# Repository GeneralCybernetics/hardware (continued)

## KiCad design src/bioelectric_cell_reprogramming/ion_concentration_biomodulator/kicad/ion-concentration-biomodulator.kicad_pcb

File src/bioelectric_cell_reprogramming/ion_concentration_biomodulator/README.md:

# Ion Concentration Biomodulator (v5)

The purpose of the chip is to enable an incubator to dispense ions over a cellular culture within the incubator.

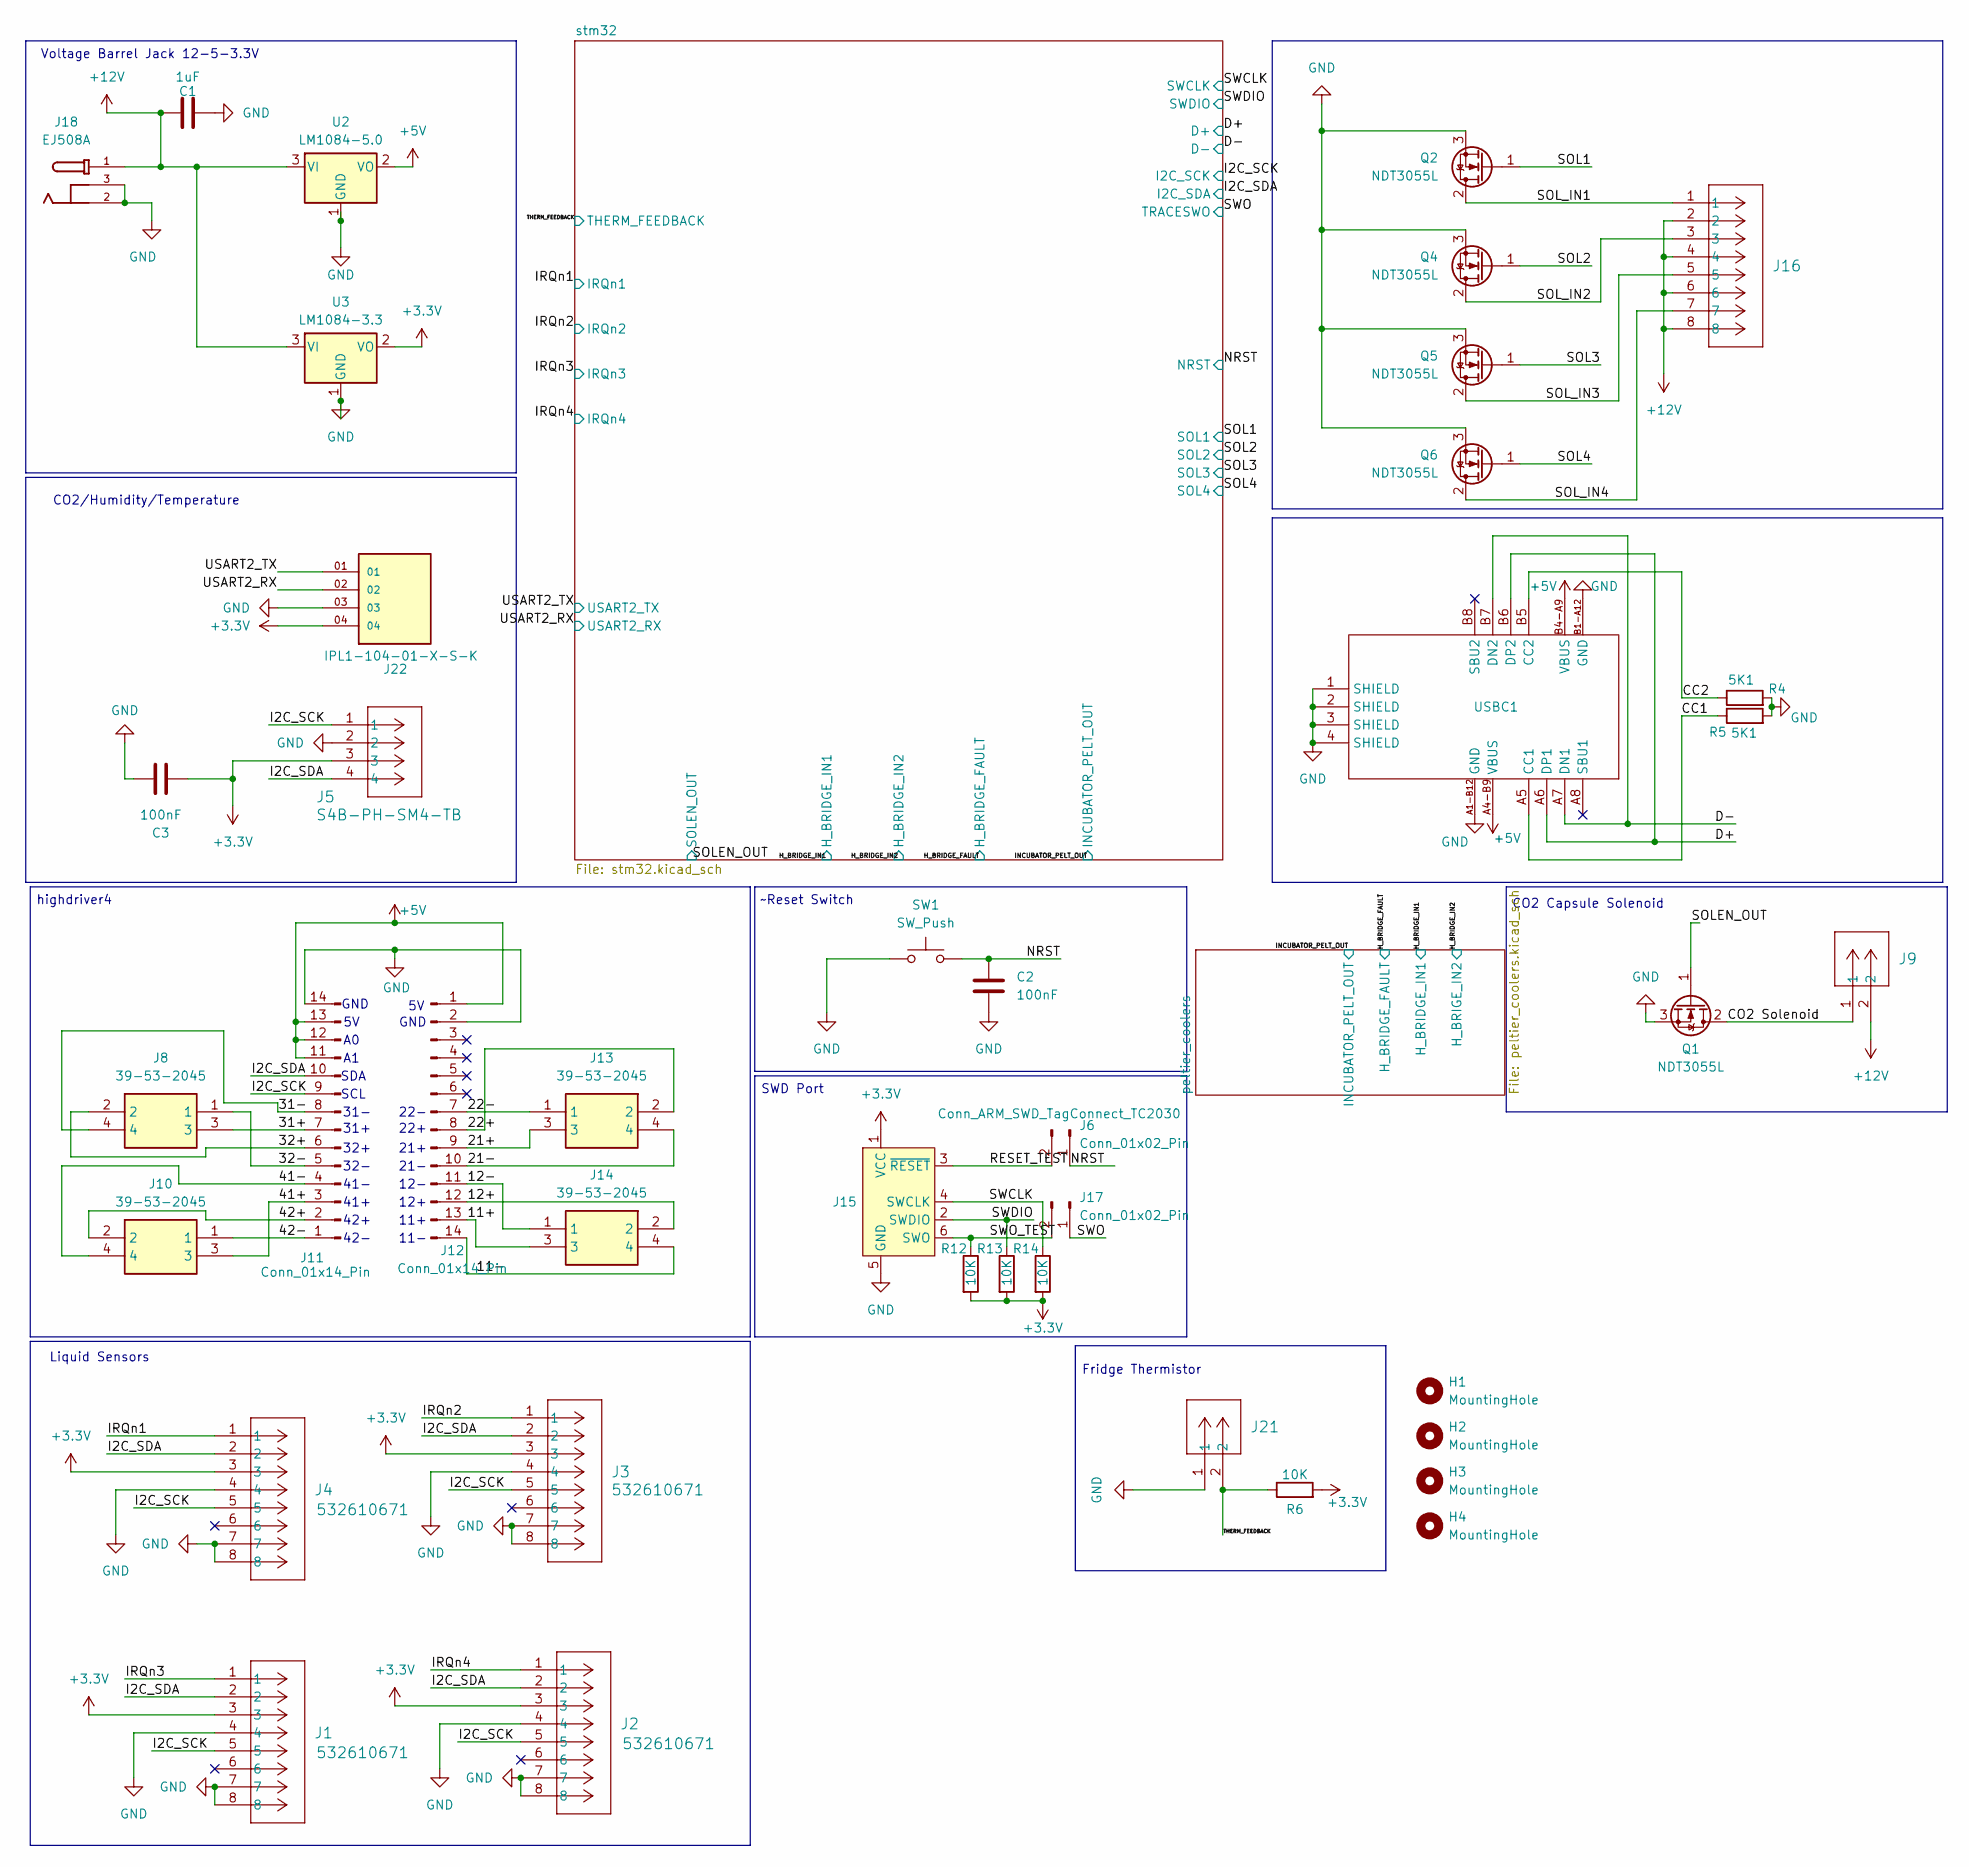
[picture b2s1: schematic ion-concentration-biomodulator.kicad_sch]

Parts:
C1: 1uF; C_1812_4532Metric
C2, C3: 100nF; C_0201_0603Metric
H1, H2, H3, H4: MountingHole; MountingHole_2.2mm_M2
J1, J2, J3, J4: 532610671; CON_532610671
J5: S4B-PH-SM4-TB; CONN4_S4B-PH-SM4-TB_JST
J6, J17: Conn_01x02_Pin; PinHeader_1x02_P2.00mm_Vertical
J8, J10, J13, J14: 39-53-2045; 39532045; Mouser Part Number 538-39532045
J9, J21: IPL1-102-01-L-S-K; CONN_IPL1-102-01-L-S-K_SAI
J11, J12: Conn_01x14_Pin; PinSocket_1x14_P2.54mm_Vertical
J15: Conn_ARM_SWD_TagConnect_TC2030; Tag-Connect_TC2030-IDC-FP_2x03_P1.27mm_Vertical
J16: IPL1-104-01-L-D-K; CONN_IPL1-104-01-x-D-x_SAI
J18: EJ508A; MPD_EJ508A; PARTREV J
J22: IPL1-104-01-X-S-K; SAMTEC_IPL1-104-01-X-S-K; PARTREV E
Q1, Q2, Q4, Q5, Q6: NDT3055L; SOT-223-3_TabPin2
R4, R5: 5K1; R_0603_1608Metric
R6, R12, R13, R14: 10K; R_0201_0603Metric
SW1: SW_Push; SW_PUSH-12mm_Wuerth-430476085716
U2: LM1084-5.0; TO254P1524X483-4N
U3: LM1084-3.3; TO254P1524X483-4N
USBC1: USB-C-SMD_MC-311D; Manufacturer Part MC-311D; LCSC Part Name Type-C 母

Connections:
+3.3V: C3.1, J1.3, J2.3, J3.3, J4.3, J5.3, J15.1 (VCC), J22.04, R6.2, R12.2, R13.2, R14.2, U3.2 (VO); also elsewhere on the board
+5V: J11.11, J11.12, J11.13, J12.1, U2.2 (VO), USBC1.A4-B9 (VBUS), USBC1.B4-A9 (VBUS); also elsewhere on the board
+12V: C1.1, J9.2, J16.2, J16.4, J16.6, J16.8, J18.1, U2.3 (VI), U3.3 (VI); also elsewhere on the board
/11+: J12.13, J14.3
/11-: J12.14, J14.4
/12+: J12.12, J14.2
/12-: J12.11, J14.1
/21+: J12.9, J13.3
/21-: J12.10, J13.4
/22+: J12.8, J13.2
/22-: J12.7, J13.1
/31+: J8.3, J11.7
/31-: J8.4, J11.8
/32+: J8.2, J11.6
/32-: J8.1, J11.5
/41+: J10.3, J11.3
/41-: J10.4, J11.4
/42+: J10.2, J11.2
/42-: J10.1, J11.1
/CC1: R4.1, USBC1.B5 (CC2); also elsewhere on the board
/CC2: R5.1, USBC1.A5 (CC1); also elsewhere on the board
/CO2 Solenoid: J9.1, Q1.2 (D)
/I2C_SCK: J1.5, J2.5, J3.5, J4.5, J5.1, J11.9; also elsewhere on the board
/I2C_SDA: J1.2, J2.2, J3.2, J4.2, J5.4, J11.10; also elsewhere on the board
/IRQn1: J4.1; also elsewhere on the board
/IRQn2: J3.1; also elsewhere on the board
/IRQn3: J1.1; also elsewhere on the board
/IRQn4: J2.1; also elsewhere on the board
/NRST: C2.1, J6.1, SW1.2; also elsewhere on the board
/RESET_TEST: J6.2, J15.3 (~RESET)
/SOL1: Q2.1 (G); also elsewhere on the board
/SOL2: Q4.1 (G); also elsewhere on the board
/SOL3: Q5.1 (G); also elsewhere on the board
/SOL4: Q6.1 (G); also elsewhere on the board
/SOLEN_OUT: Q1.1 (G); also elsewhere on the board
/SOL_IN1: J16.1, Q2.2 (D)
/SOL_IN2: J16.3, Q4.2 (D)
/SOL_IN3: J16.5, Q5.2 (D)
/SOL_IN4: J16.7, Q6.2 (D)
/SWCLK: J15.4 (SWCLK), R14.1; also elsewhere on the board
/SWDIO: J15.2 (SWDIO), R13.1; also elsewhere on the board
/SWO: J17.1; also elsewhere on the board
/SWO_TEST: J15.6 (SWO), J17.2, R12.1
/THERM_FEEDBACK: J21.2, R6.1; also elsewhere on the board
/USART2_RX: J22.02; also elsewhere on the board
/USART2_TX: J22.01; also elsewhere on the board
GND: C1.2, C2.2, C3.2, J1.4, J1.7, J1.8, J2.4, J2.7, J2.8, J3.4, J3.7, J3.8, J4.4, J4.7, J4.8, J5.2, J11.14, J12.2, J15.5 (GND), J18.2, J18.3, J21.1, J22.03, Q1.3 (S), Q2.3 (S), Q4.3 (S), Q5.3 (S), Q6.3 (S), R4.2, R5.2, SW1.1, U2.1 (GND), U3.1 (GND), USBC1.1 (SHIELD), USBC1.2 (SHIELD), USBC1.3 (SHIELD), USBC1.4 (SHIELD), USBC1.A1-B12 (GND), USBC1.B1-A12 (GND); also elsewhere on the board
unnamed: USBC1.A6 (DP1), USBC1.B6 (DP2)
unnamed: USBC1.A7 (DN1), USBC1.B7 (DN2)

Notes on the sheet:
Voltage Barrel Jack 12-5-3.3V
21+
CO2/Humidity/Temperature
41+
31-
SDA
Fridge Thermistor
SWD Port
41-
GND
32-
SCL
42-
Liquid Sensors
11-
22+
highdriver4
12-
21-
~Reset Switch
32+
22-
CO2 Capsule Solenoid
11+
42+
31+
12+

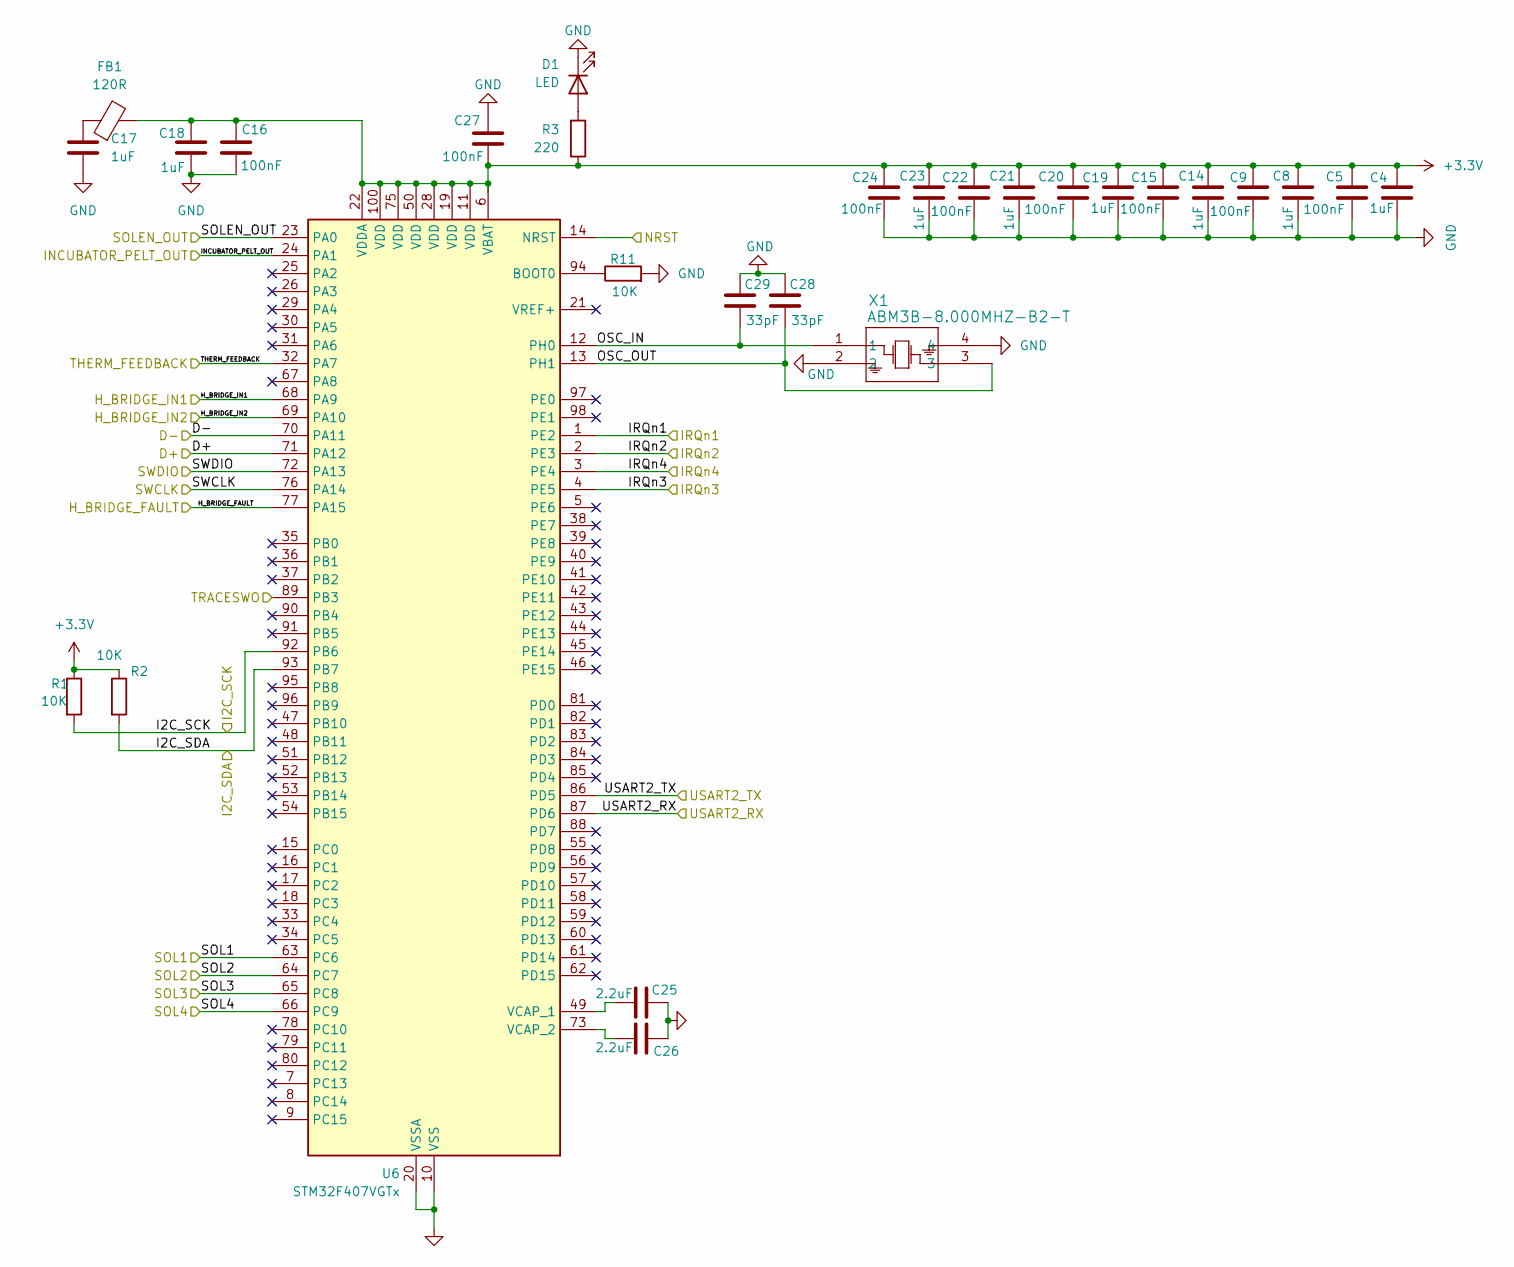
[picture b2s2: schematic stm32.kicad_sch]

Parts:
C4, C8, C14, C17, C18, C19, C21, C23: 1uF; C_0201_0603Metric
C5, C9, C15, C16, C20, C22, C24, C27: 100nF; C_0201_0603Metric
C25, C26: 2.2uF; C_0201_0603Metric
C28, C29: 33pF; C_0201_0603Metric
D1: LED; LED_0201_0603Metric
FB1: 120R; L_0603_1608Metric
R1, R2, R11: 10K; R_0201_0603Metric
R3: 220; R_0201_0603Metric
U6: STM32F407VGTx; LQFP-100_14x14mm_P0.5mm
X1: ABM3B-8.000MHZ-B2-T; ABM3B_ABR

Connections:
+3.3V: C4.1, C5.1, C8.1, C9.1, C14.1, C15.1, C16.1, C18.1, C19.1, C20.1, C21.1, C22.1, C23.1, C24.1, C27.2, FB1.2, R1.1, R2.1, R3.1, U6.6 (VBAT), U6.11 (VDD), U6.19 (VDD), U6.22 (VDDA), U6.28 (VDD), U6.50 (VDD), U6.75 (VDD), U6.100 (VDD); also elsewhere on the board
/D+: U6.71 (PA12); also elsewhere on the board
/D-: U6.70 (PA11); also elsewhere on the board
/H_BRIDGE_FAULT: U6.77 (PA15); also elsewhere on the board
/H_BRIDGE_IN1: U6.68 (PA9); also elsewhere on the board
/H_BRIDGE_IN2: U6.69 (PA10); also elsewhere on the board
/I2C_SCK: R1.2, U6.92 (PB6); also elsewhere on the board
/I2C_SDA: R2.2, U6.93 (PB7); also elsewhere on the board
/INCUBATOR_PELT_OUT: U6.24 (PA1); also elsewhere on the board
/IRQn1: U6.1 (PE2); also elsewhere on the board
/IRQn2: U6.2 (PE3); also elsewhere on the board
/IRQn3: U6.4 (PE5); also elsewhere on the board
/IRQn4: U6.3 (PE4); also elsewhere on the board
/NRST: U6.14 (NRST); also elsewhere on the board
/SOL1: U6.63 (PC6); also elsewhere on the board
/SOL2: U6.64 (PC7); also elsewhere on the board
/SOL3: U6.65 (PC8); also elsewhere on the board
/SOL4: U6.66 (PC9); also elsewhere on the board
/SOLEN_OUT: U6.23 (PA0); also elsewhere on the board
/SWCLK: U6.76 (PA14); also elsewhere on the board
/SWDIO: U6.72 (PA13); also elsewhere on the board
/SWO: U6.89 (PB3); also elsewhere on the board
/THERM_FEEDBACK: U6.32 (PA7); also elsewhere on the board
/USART2_RX: U6.87 (PD6); also elsewhere on the board
/USART2_TX: U6.86 (PD5); also elsewhere on the board
/stm32/OSC_IN: C29.2, U6.12 (PH0), X1.1
/stm32/OSC_OUT: C28.2, U6.13 (PH1), X1.3
GND: C4.2, C5.2, C8.2, C9.2, C14.2, C15.2, C16.2, C17.2, C18.2, C19.2, C20.2, C21.2, C22.2, C23.2, C24.2, C25.2, C26.2, C27.1, C28.1, C29.1, D1.1 (K), R11.2, U6.10 (VSS), U6.20 (VSSA), U6.27 (VSS), U6.74 (VSS), U6.99 (VSS), X1.2, X1.4; also elsewhere on the board
unnamed: C17.1, FB1.1
unnamed: D1.2 (A), R3.2
unnamed: R11.1, U6.94 (BOOT0)
unnamed: C25.1, U6.49 (VCAP_1)
unnamed: C26.1, U6.73 (VCAP_2)

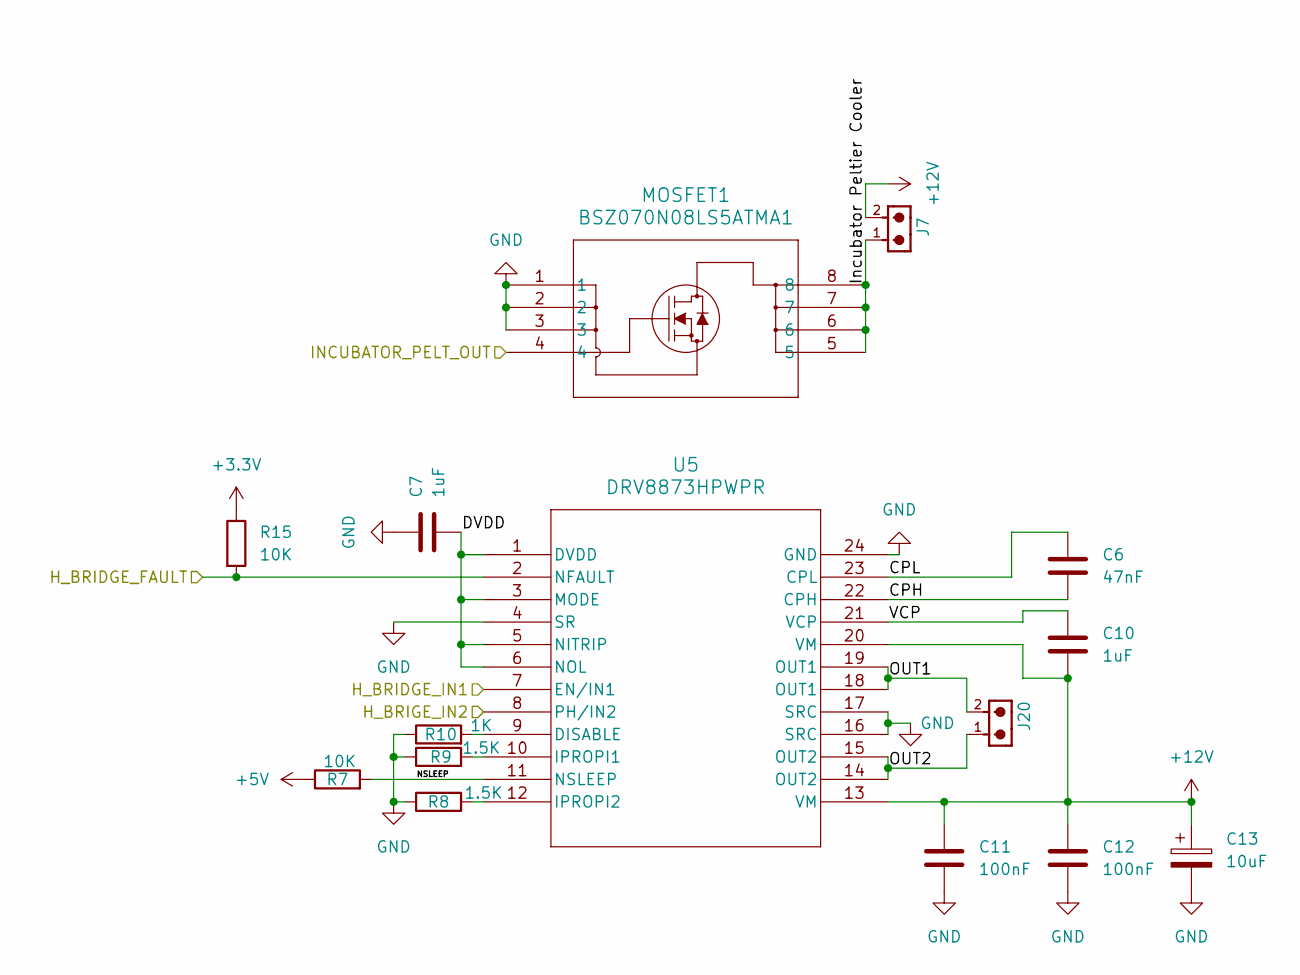
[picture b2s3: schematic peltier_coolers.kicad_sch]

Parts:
C6: 47nF; C_0402_1005Metric
C7: 1uF; C_0201_0603Metric
C10: 1uF; C_0402_1005Metric
C11, C12: 100nF; C_0402_1005Metric
C13: 10uF; CP_Elec_3x5.3
J7, J20: 6620XX11122_66200211122; 66200211122; PART-NUMBER 66200211122
MOSFET1: BSZ070N08LS5ATMA1; TSDSON-8-FL_INF
R7, R15: 10K; R_0201_0603Metric
R8, R9: 1.5K; R_0201_0603Metric
R10: 1K; R_0201_0603Metric
U5: DRV8873HPWPR; PWP24_TEX

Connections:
+3.3V: R15.1; also elsewhere on the board
+5V: R7.1; also elsewhere on the board
+12V: C10.2, C11.1, C12.1, C13.1, J7.2, U5.13 (VM), U5.20 (VM); also elsewhere on the board
/H_BRIDGE_FAULT: R15.2, U5.2 (NFAULT); also elsewhere on the board
/H_BRIDGE_IN1: U5.7 (EN/IN1); also elsewhere on the board
/H_BRIDGE_IN2: U5.8 (PH/IN2); also elsewhere on the board
/INCUBATOR_PELT_OUT: MOSFET1.4; also elsewhere on the board
/peltier_coolers/CPH: C6.2, U5.22 (CPH)
/peltier_coolers/CPL: C6.1, U5.23 (CPL)
/peltier_coolers/DVDD: C7.2, U5.1 (DVDD), U5.3 (MODE), U5.5 (NITRIP), U5.6 (NOL)
/peltier_coolers/Incubator Peltier Cooler: J7.1, MOSFET1.5, MOSFET1.6, MOSFET1.7, MOSFET1.8
/peltier_coolers/NSLEEP: R7.2, U5.11 (NSLEEP)
/peltier_coolers/OUT1: J20.2, U5.18 (OUT1), U5.19 (OUT1)
/peltier_coolers/OUT2: J20.1, U5.14 (OUT2), U5.15 (OUT2)
/peltier_coolers/VCP: C10.1, U5.21 (VCP)
GND: C7.1, C11.2, C12.2, C13.2, MOSFET1.1, MOSFET1.2, MOSFET1.3, R8.1, R9.1, R10.1, U5.4 (SR), U5.16 (SRC), U5.17 (SRC), U5.24 (GND); also elsewhere on the board
unnamed: R10.2, U5.9 (DISABLE)
unnamed: R9.2, U5.10 (IPROPI1)
unnamed: R8.2, U5.12 (IPROPI2)

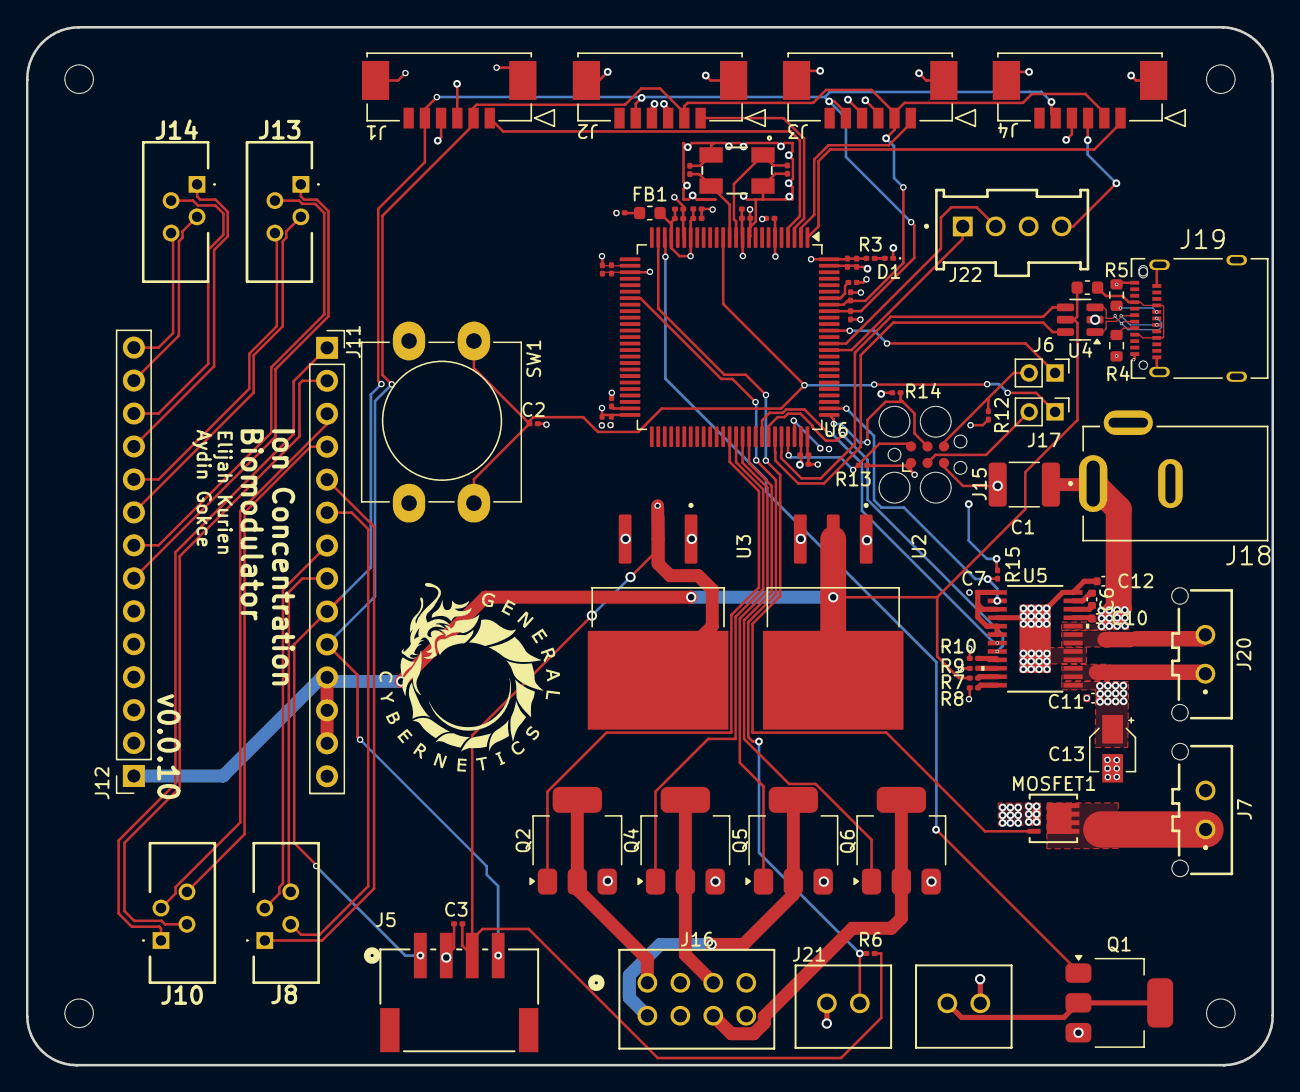
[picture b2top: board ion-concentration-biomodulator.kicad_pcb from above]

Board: 4 copper layers, 96.0 x 80.0 mm, 86 parts (0 on the bottom side), 74 nets.

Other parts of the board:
F1: 500mA; Fuse_0603_1608Metric
J19: USB_C_Receptacle_USB2.0_14P; AMPHENOL_12401610E4_2A
U4: USBLC6-2SC6; SOT-23-6

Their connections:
+5V: F1.2, U4.5 (VBUS); also elsewhere on the board
/CC1: J19.A5 (CC1); also elsewhere on the board
/CC2: J19.B5 (CC2); also elsewhere on the board
/D+: U4.4 (I/O2); also elsewhere on the board
/D+_in: J19.A6 (DA+), J19.B6 (DB+), U4.3 (I/O2)
/D-: U4.6 (I/O1); also elsewhere on the board
/D-_in: J19.A7 (DA-), J19.B7 (DB-), U4.1 (I/O1)
/VBUS: F1.1, J19.A4 (VBUS_A4), J19.A9 (VBUS_A9), J19.B4 (VBUS_B4), J19.B9 (VBUS_B9)
GND: J19.A1 (GND_A1), J19.A12 (GND_A12), J19.B1 (GND_B1), J19.B12 (GND_B12), J19.S1 (SHIELD), J19.S2 (SHIELD__1), J19.S3 (SHIELD__2), J19.S4 (SHIELD__3), U4.2 (GND); also elsewhere on the board

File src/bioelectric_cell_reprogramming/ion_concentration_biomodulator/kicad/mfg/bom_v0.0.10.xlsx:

Comment | Designator | Footprint | JLCPCB Part #
10K | R14,R13,R12,R11,R2,R1,R7,R6 | R_0201_0603Metric | C3152014
2.2uF | C26,C25 | C_0201_0603Metric | C516003
BSZ070N08LS5ATMA1 | MOSFET1 | TSDSON-8-FL_INF | C534678
100nF | C27,C15,C24,C22,C9,C5,C20,C16,C3,C2 | C_0201_0603Metric | C181047
1uF | C14,C23,C21,C8,C4,C19,C18,C17,C7 | C_0201_0603Metric | C2177042
220.0 | R3 | R_0201_0603Metric | C274342
STM32F407VGTx | U6 | LQFP-100_14x14mm_P0.5mm | C12345
120R | FB1 | L_0603_1608Metric | C1028
LED | D1 | LED_0201_0603Metric | C3646923
LM1084-5.0 | U2 | TO254P1524X483-4N | C2860176
5.32610671E8 | J3,J2,J1,J4 | CON_532610671 | C17393620
47nF | C6 | C_0402_1005Metric | C107020
1uF | C1 | C_1812_4532Metric | C342623
USBLC6-2SC6 | U4 | SOT-23-6 | C2827654
SW_Push | SW1 | SW_PUSH-12mm_Wuerth-430476085716 | C18186453
Conn_01x02_Pin | J17,J6 | PinHeader_1x02_P2.00mm_Vertical | C7501287
NDT3055L | Q4,Q2,Q1,Q5,Q6 | SOT-223-3_TabPin2 | C7472932
1.5K | R9,R8 | R_0201_0603Metric | C225067
1K | R10 | R_0201_0603Metric | C5151552
1uF | C10 | C_0402_1005Metric | C326568
USB_C_Receptacle_USB2.0_14P | J19 | AMPHENOL_12401610E4_2A | C5119948
LM1084-3.3 | U3 | TO254P1524X483-4N | C259972
100nF | C12,C11 | C_0402_1005Metric | C507422
10uF | C13 | CP_Elec_3x5.3 | C249450
DRV8873HPWPR | U5 | PWP24_TEX | C2150604
5K1 | R5,R4 | R_0603_1608Metric | C22775
500mA | F1 | Fuse_0603_1608Metric | C2757929
S4B-PH-SM4-TB | J5 | CONN4_S4B-PH-SM4-TB_JST | C265102
EJ508A | J18 | MPD_EJ508A
6620XX11122_66200211122 | J7,J20 | 6.6200211122E10
IPL1-102-01-L-S-K | J9,J21 | CONN_IPL1-102-01-L-S-K_SAI
Conn_01x14_Pin | J11,J12 | PinSocket_1x14_P2.54mm_Vertical
IPL1-104-01-L-D-K | J16 | CONN_IPL1-104-01-x-D-x_SAI
39-53-2045 | J14,J10,J8,J13 | 3.9532045E7

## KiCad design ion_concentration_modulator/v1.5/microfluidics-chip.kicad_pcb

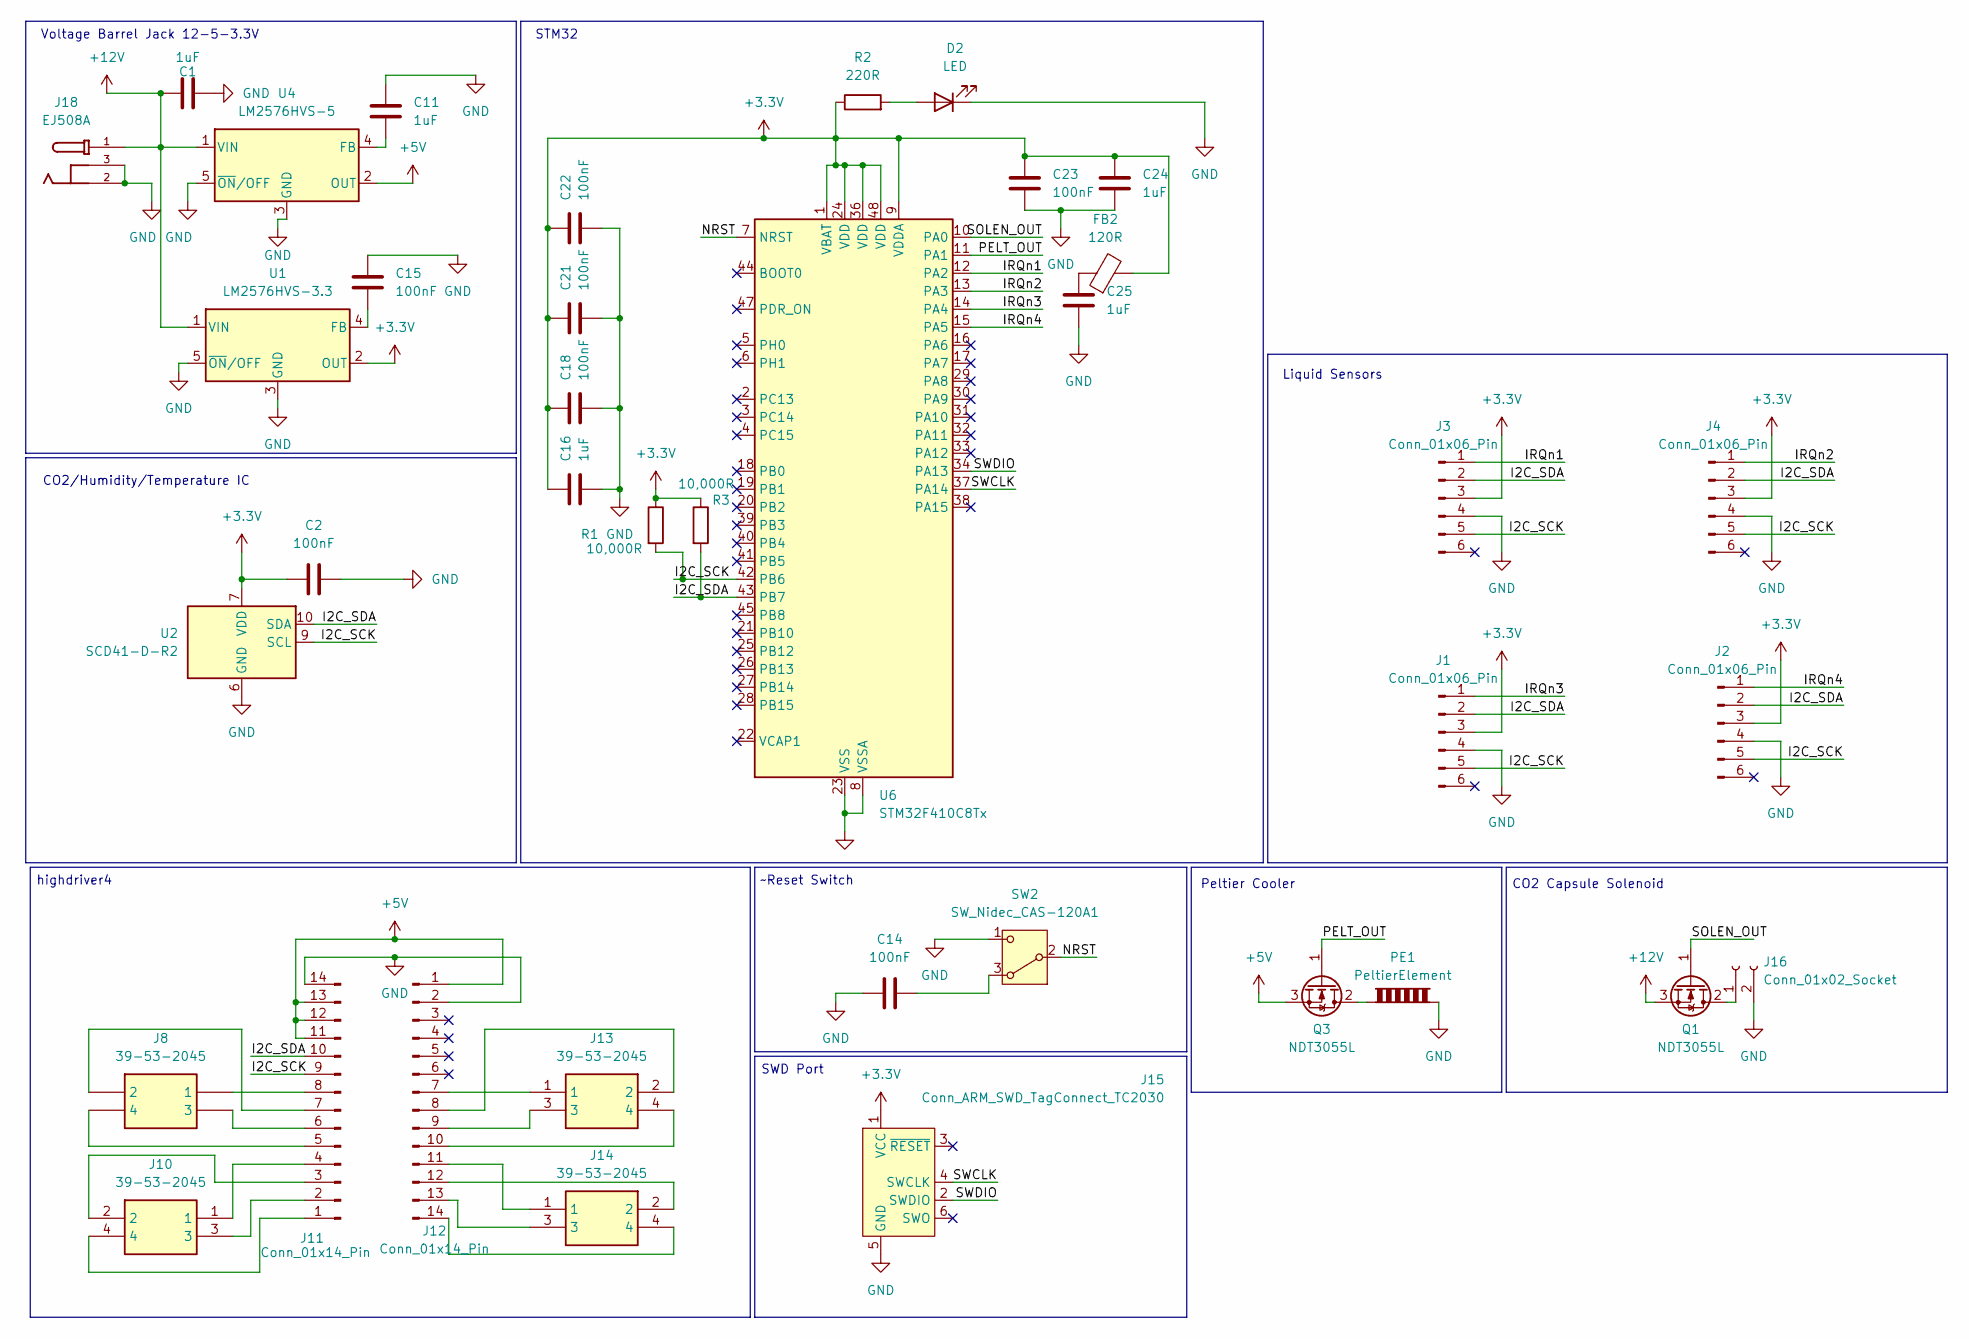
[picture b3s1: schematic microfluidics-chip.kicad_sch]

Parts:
C1, C11, C16, C24, C25: 1uF; C_0402_1005Metric
C2, C14, C15, C18, C21, C22, C23: 100nF; C_0402_1005Metric
D2: LED; LED_D3.0mm
FB2: 120R; L_7.3x7.3_H4.5
J1, J2, J3, J4: Conn_01x06_Pin; Hirose_DF13-06P-1.25DSA_1x06_P1.25mm_Vertical
J8, J10, J13, J14: 39-53-2045; 39532045; Mouser Part Number 538-39532045
J11, J12: Conn_01x14_Pin; PinSocket_1x14_P2.54mm_Vertical
J15: Conn_ARM_SWD_TagConnect_TC2030; Tag-Connect_TC2030-IDC-FP_2x03_P1.27mm_Vertical
J16: Conn_01x02_Socket; PinSocket_1x02_P2.54mm_Vertical
J18: EJ508A; MPD_EJ508A; PARTREV J
PE1: PeltierElement; PinSocket_1x02_P2.54mm_Vertical
Q1, Q3: NDT3055L; SOT-223-3_TabPin2
R1, R3: 10,000R; R_Axial_DIN0207_L6.3mm_D2.5mm_P7.62mm_Horizontal
R2: 220R; R_Axial_DIN0204_L3.6mm_D1.6mm_P5.08mm_Horizontal
SW2: SW_Nidec_CAS-120A1; Nidec_Copal_CAS-120A
U1: LM2576HVS-3.3; TO-263-5_TabPin3
U2: SCD41-D-R2; Sensirion_SCD4x-1EP_10.1x10.1mm_P1.25mm_EP4.8x4.8mm
U4: LM2576HVS-5; TO-263-5_TabPin3
U6: STM32F410C8Tx; LQFP-48_7x7mm_P0.5mm

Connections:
+3.3V: C2.1, C16.1, C18.1, C21.1, C22.1, C23.1, C24.1, FB2.2, J1.3, J2.3, J3.3, J4.3, J15.1 (VCC), R1.1, R2.1, R3.1, U1.2 (OUT), U2.7 (VDD), U2.19 (VDD), U6.1 (VBAT), U6.9 (VDDA), U6.24 (VDD), U6.36 (VDD), U6.48 (VDD)
+5V: J11.11, J11.12, J11.13, J12.1, Q3.3 (S), U4.2 (OUT)
+12V: C1.1, J18.1, Q1.3 (S), U1.1 (VIN), U4.1 (VIN)
/I2C_SCK: J1.5, J2.5, J3.5, J4.5, J11.9, R1.2, U2.9 (SCL), U6.42 (PB6)
/I2C_SDA: J1.2, J2.2, J3.2, J4.2, J11.10, R3.2, U2.10 (SDA), U6.43 (PB7)
/IRQn1: J3.1, U6.12 (PA2)
/IRQn2: J4.1, U6.13 (PA3)
/IRQn3: J1.1, U6.14 (PA4)
/IRQn4: J2.1, U6.15 (PA5)
/NRST: SW2.2 (B), U6.7 (NRST)
/PELT_OUT: Q3.1 (G), U6.11 (PA1)
/SOLEN_OUT: Q1.1 (G), U6.10 (PA0)
/SWCLK: J15.4 (SWCLK), U6.37 (PA14)
/SWDIO: J15.2 (SWDIO), U6.34 (PA13)
GND: C1.2, C2.2, C11.1, C14.1, C15.1, C16.2, C18.2, C21.2, C22.2, C23.2, C24.2, C25.2, D2.1 (K), J1.4, J2.4, J3.4, J4.4, J11.14, J12.2, J15.5 (GND), J16.2, J18.2, J18.3, PE1.2, SW2.1 (C), U1.3 (GND), U1.5 (~ON/OFF), U2.6 (GND), U2.20 (GND), U2.21 (GND), U4.3 (GND), U4.5 (~ON/OFF), U6.8 (VSSA), U6.23 (VSS), U6.35 (VSS), U6.46 (VSS)
unnamed: C25.1, FB2.1
unnamed: D2.2 (A), R2.2
unnamed: J10.4, J11.1
unnamed: J10.3, J11.2
unnamed: J10.2, J11.3
unnamed: J10.1, J11.4
unnamed: J8.4, J11.5
unnamed: J8.3, J11.6
unnamed: J8.2, J11.7
unnamed: J8.1, J11.8
unnamed: J12.7, J13.1
unnamed: J12.8, J13.2
unnamed: J12.9, J13.3
unnamed: J12.10, J13.4
unnamed: J12.11, J14.1
unnamed: J12.12, J14.2
unnamed: J12.13, J14.3
unnamed: J12.14, J14.4
unnamed: J16.1, Q1.2 (D)
unnamed: PE1.1, Q3.2 (D)
unnamed: C14.2, SW2.3 (A)
unnamed: C15.2, U1.4 (FB)
unnamed: C11.2, U4.4 (FB)

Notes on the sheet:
Voltage Barrel Jack 12-5-3.3V
CO2/Humidity/Temperature IC
Peltier Cooler
STM32
SWD Port
Liquid Sensors
highdriver4
~Reset Switch
CO2 Capsule Solenoid

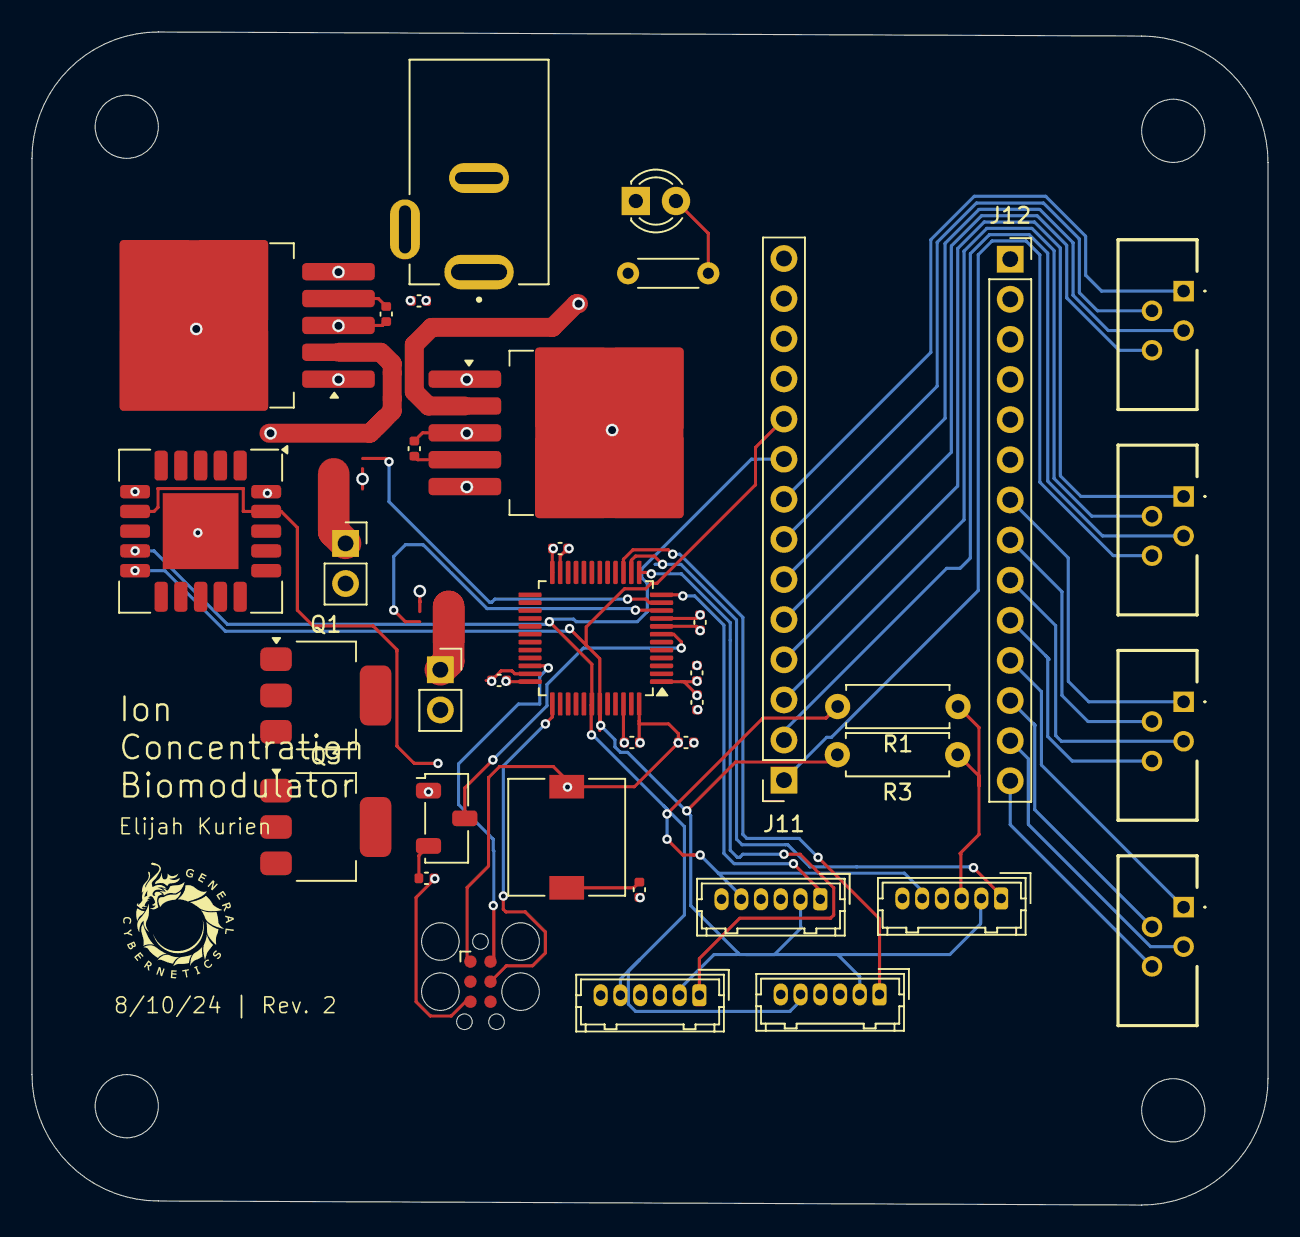
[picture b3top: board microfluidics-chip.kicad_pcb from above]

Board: 4 copper layers, 78.2 x 74.3 mm, 38 parts (0 on the bottom side), 38 nets.

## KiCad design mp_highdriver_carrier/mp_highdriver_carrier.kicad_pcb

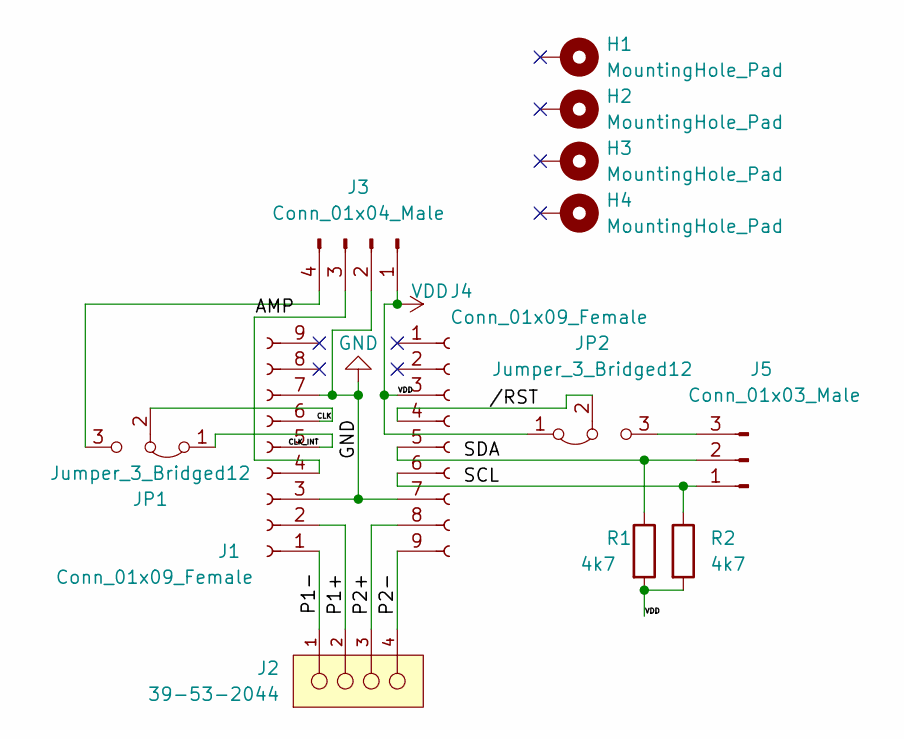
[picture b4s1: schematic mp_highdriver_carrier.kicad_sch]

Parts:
H1, H2, H3, H4: MountingHole_Pad; MountingHole_2.7mm_M2.5_Pad
J1, J4: Conn_01x09_Female; PinSocket_1x09_P2.54mm_Vertical
J2: 39-53-2044; Molex-39-53-2044-Manufacturer_Recommended; Voltage Max 200V
J3: Conn_01x04_Male; PinHeader_1x04_P2.54mm_Vertical
J5: Conn_01x03_Male; PinHeader_1x03_P2.54mm_Vertical
JP1, JP2: Jumper_3_Bridged12; PinHeader_1x03_P2.54mm_Vertical
R1, R2: 4k7; R_0402_1005Metric

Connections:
/AMP: J1.4, J3.3
/CLK: J1.6, JP1.2 (C)
/CLK_INT: J1.5, JP1.1 (A)
/P1+: J1.2, J2.2
/P1-: J1.1, J2.1
/P2+: J2.3, J4.8
/P2-: J2.4, J4.9
/SCL: J4.6, J5.1, R2.1
/SDA: J4.5, J5.2, R1.1
//RST: J4.4, JP2.2 (C)
GND: J1.3, J1.7, J3.2, J4.7
unnamed: J3.4, JP1.3 (B)
unnamed: J5.3, JP2.3 (B)
VDD: J3.1, J4.3, JP2.1 (A), R1.2, R2.2

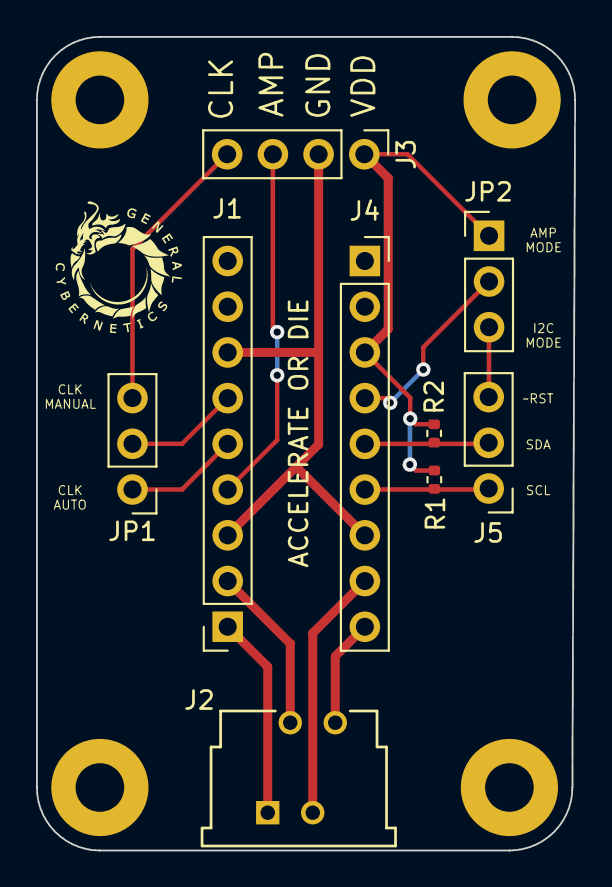
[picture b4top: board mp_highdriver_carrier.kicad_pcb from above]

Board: 2 copper layers, 29.9 x 45.2 mm, 13 parts (0 on the bottom side), 14 nets.
